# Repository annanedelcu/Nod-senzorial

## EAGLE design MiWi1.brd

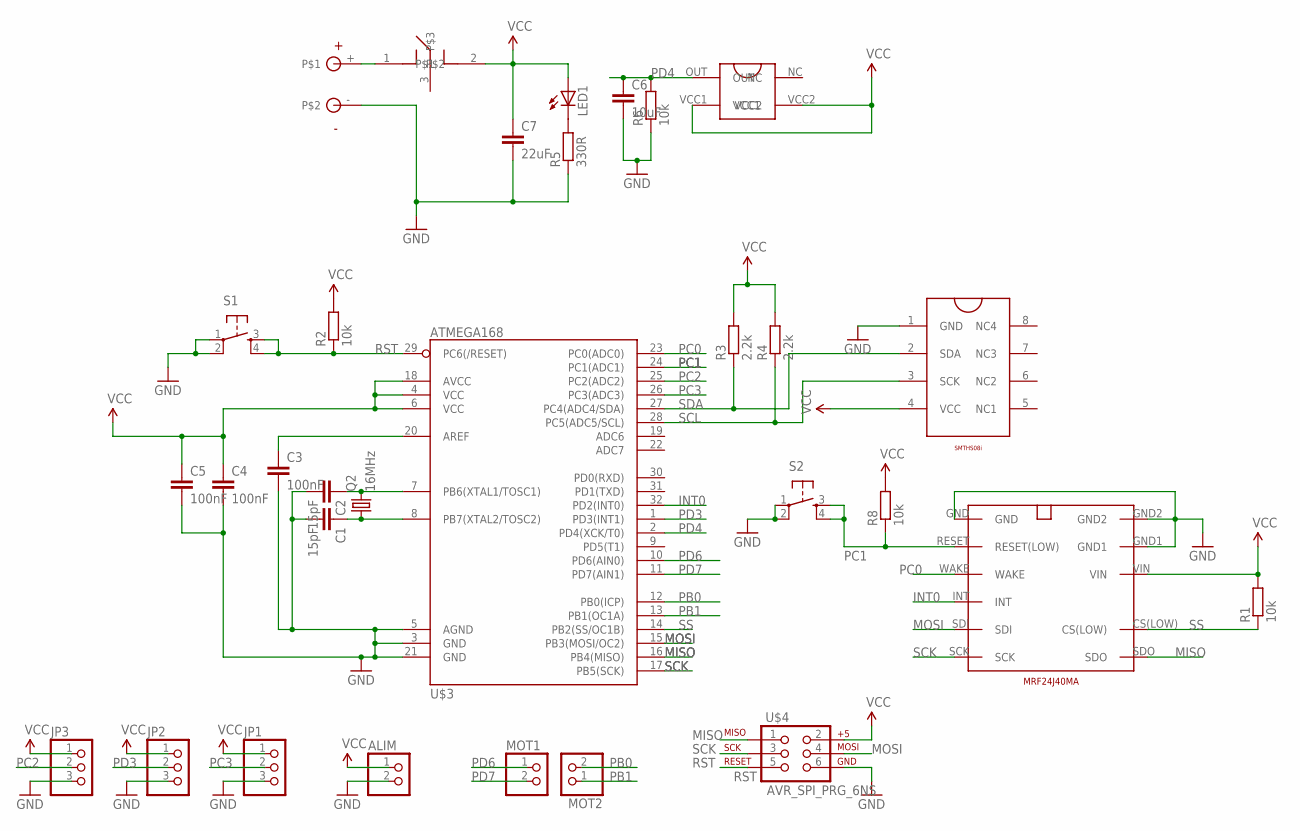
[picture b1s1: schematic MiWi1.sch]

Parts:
ALIM: PINHD-1X2; 1X02
C1, C2: 15pF; C0805
C3, C4, C5: 100nF; C0805
C6: 10uF; C0805
C7: 22uF; C0805
JP1, JP2, JP3: PINHD-1X3; 1X03
LED1: LEDCHIP-LED0805; CHIP-LED0805
MOT1, MOT2: PINHD-1X2; 1X02
Q2: 16MHz; CRYSTAL-SMD-5X3
R1, R2, R6, R8: 10k; R0805W
R3, R4: 2.2k; R0805W
R5: 330R; R0805W
S1, S2: TAC_SWITCHSMD; TACTILE_SWITCH_SMD
U$1: MRF24J40MA
U$2: SMTH08I; SMTHS08I_PK
U$3: ATMEGA168; TQFP32-08
U$4: AVR_SPI_PRG_6NS; 2X3-NS
U$5: SPDT_PCM12SMRT
U$6: 2XAAA_BATTERY_HOLDER
U$7: APDS-9004

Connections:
GND: ALIM.2, C1.2, C2.2, C3.2, C4.2, C5.2, C6.2, C7.2, JP1.3, JP2.3, JP3.3, R5.1, R6.1, S1.1, S1.2, S2.1, S2.2, U$1.GND, U$1.GND1, U$1.GND2, U$2.1 (GND), U$3.3 (GND), U$3.5 (AGND), U$3.21 (GND), U$4.6, U$6.-
INT0: U$1.INT, U$3.32 (PD2(INT0))
MISO: U$1.SDO, U$3.16 (PB4(MISO)), U$4.1
MOSI: U$1.SDI, U$3.15 (PB3(MOSI/OC2)), U$4.4
unnamed: C2.1, Q2.3 (2), U$3.7 (PB6(XTAL1/TOSC1))
unnamed: C1.1, Q2.1, U$3.8 (PB7(XTAL2/TOSC2))
unnamed: C3.1, U$3.20 (AREF)
unnamed: U$5.1, U$6.+
unnamed: LED1.C, R5.2
PB0: MOT2.2, U$3.12 (PB0(ICP))
PB1: MOT2.1, U$3.13 (PB1(OC1A))
PC0: U$1.WAKE, U$3.23 (PC0(ADC0))
PC1: R8.1, S2.3, S2.4, U$1.RESET (RESET(LOW)), U$3.24 (PC1(ADC1))
PC2: JP3.2, U$3.25 (PC2(ADC2))
PC3: JP1.2, U$3.26 (PC3(ADC3))
PD3: JP2.2, U$3.1 (PD3(INT1))
PD4: C6.1, R6.2, U$3.2 (PD4(XCK/T0)), U$7.OUT
PD6: MOT1.1, U$3.10 (PD6(AIN0))
PD7: MOT1.2, U$3.11 (PD7(AIN1))
RST: R2.1, S1.3, S1.4, U$3.29 (PC6(/RESET)), U$4.5
SCK: U$1.SCK, U$3.17 (PB5(SCK)), U$4.3
SCL: R4.1, U$2.3 (SCK), U$3.28 (PC5(ADC5/SCL))
SDA: R3.1, U$2.2 (SDA), U$3.27 (PC4(ADC4/SDA))
SS: R1.1, U$1.CS(LOW), U$3.14 (PB2(SS/OC1B))
VCC: ALIM.1, C4.1, C5.1, C7.1, JP1.1, JP2.1, JP3.1, LED1.A, R1.2, R2.2, R3.2, R4.2, R8.2, U$1.VIN, U$2.4 (VCC), U$3.4 (VCC), U$3.6 (VCC), U$3.18 (AVCC), U$4.2, U$5.2, U$7.VCC1, U$7.VCC2

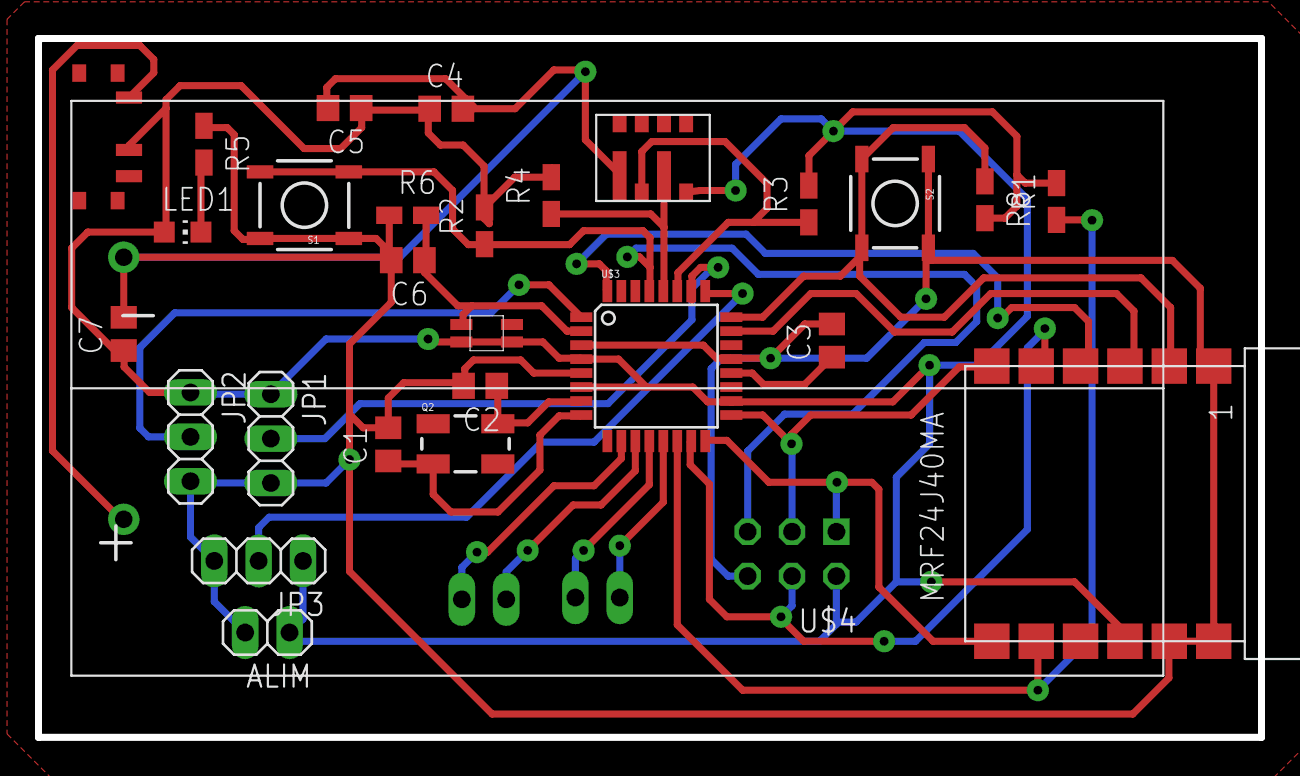
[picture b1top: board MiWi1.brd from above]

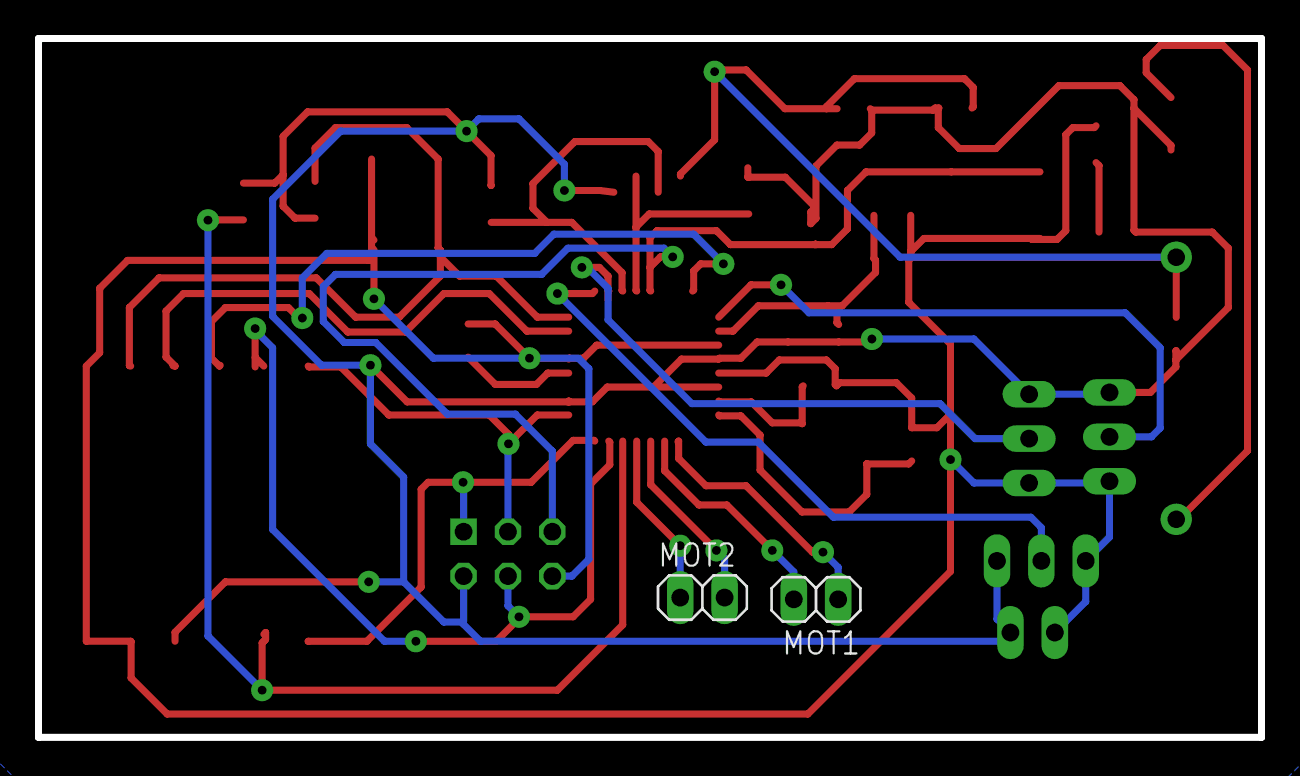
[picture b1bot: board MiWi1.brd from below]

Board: 2 copper layers, 70.0 x 40.0 mm, 31 parts (2 on the bottom side), 25 nets.

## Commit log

2014-04-13 Add article + files
